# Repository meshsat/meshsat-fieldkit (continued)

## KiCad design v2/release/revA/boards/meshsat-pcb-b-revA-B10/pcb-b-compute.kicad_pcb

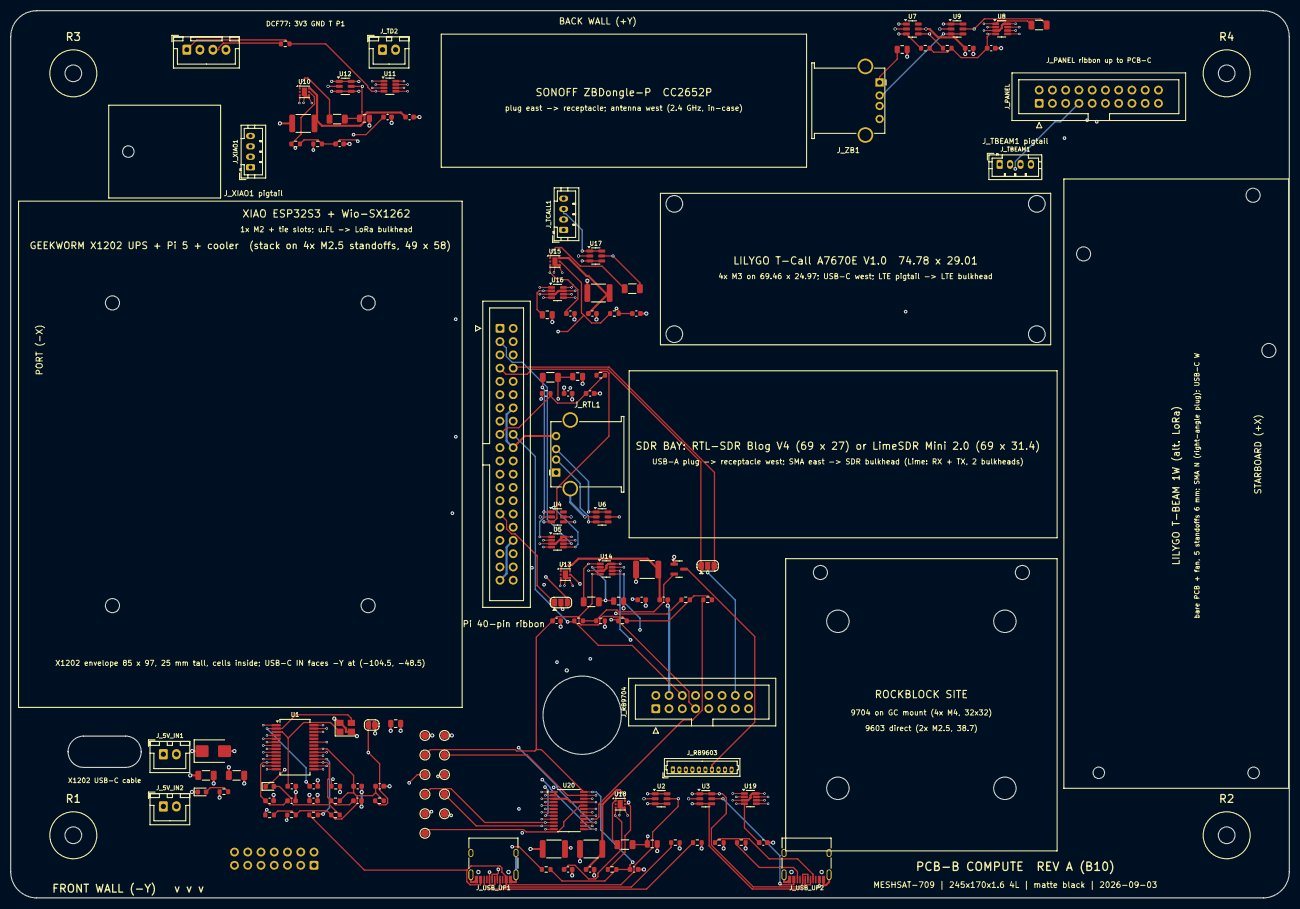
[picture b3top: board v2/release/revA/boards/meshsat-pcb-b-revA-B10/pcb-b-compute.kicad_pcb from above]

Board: 4 copper layers, 245.0 x 170.0 mm, 161 parts (1 on the bottom side), 98 nets.

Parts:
C1, C2: 100u 10V; C_1206_3216Metric
C3, C4: 22p; C_0603_1608Metric
C5, C7, C9, C12, C14, C16, C18, C21, C24, C26, C33, C34: 100n; C_0603_1608Metric
C6, C8, C11, C29, C30, C31, C32: 1u; C_0603_1608Metric
C10, C13, C15, C17, C19, C22, C25: 10u; C_0805_2012Metric
C20, C23, C27, C28: 1n; C_0603_1608Metric
D1: SMBJ5.0A; D_SMB
F2, F4, F5: 2A hold 1812; Fuse_1812_4532Metric
F3: 1.1A hold 1812; Fuse_1812_4532Metric
F6: 0.5A hold 1812; Fuse_1812_4532Metric
H1: M3 rod R1; MountingHole_3.2mm_M3
H2: M3 rod R2; MountingHole_3.2mm_M3
H3: M3 rod R3; MountingHole_3.2mm_M3
H4: M3 rod R4; MountingHole_3.2mm_M3
H5, H6, H7, H8: M2.5 standoff, Pi/X1202 stack; MountingHole_2.7mm_M2.5
H9, H10, H11, H12: M3, T-Call corner; MountingHole_3.2mm_M3
H13, H14, H15: M2.5 standoff, T-Beam 1W; MountingHole_2.7mm_M2.5
H16, H17: M2 standoff, T-Beam 1W; MountingHole_2.2mm_M2
H18: M2 standoff, Wio-SX1262; MountingHole_2.2mm_M2
H19, H20, H21, H22: M4, GC 9704 bracket; MountingHole_4.3mm_M4
H23, H24: M2.5, RockBLOCK 9603; MountingHole_2.7mm_M2.5
JP1: BUSJ to GND = bus-powered; SolderJumper-2_P1.3mm_Open_RoundedPad1.0x1.5mm
JP3: UART TX select: A=UART2 (BCM4) B=UART0 (BCM14); SolderJumper-3_P1.3mm_Open_RoundedPad1.0x1.5mm
JP4: UART RX select: A=UART2 (BCM5) B=UART0 (BCM15); SolderJumper-3_P1.3mm_Open_RoundedPad1.0x1.5mm
J_5V_IN1, J_5V_IN2: X1202 5V OUT (XH2.54); JST_XH_B2B-XH-A_1x02_P2.50mm_Vertical
J_AB1: A-B interconnect (IDC 2x7, underside); IDC-Header_2x07_P2.54mm_Vertical
J_DCF77: DCF77 remote (XH2.5): 3V3 GND T P1; JST_XH_B4B-XH-A_1x04_P2.50mm_Vertical
J_GPIO1: Pi 5 GPIO ribbon 2x20; IDC-Header_2x20_P2.54mm_Vertical
J_PANEL: panel ribbon to PCB-C (IDC 2x10); IDC-Header_2x10_P2.54mm_Vertical
J_RB9603: RockBLOCK 9603 PicoBlade 10; Molex_PicoBlade_53047-1010_1x10_P1.25mm_Vertical
J_RB9704: RockBLOCK 9704 16-pin (IDC 2x8); IDC-Header_2x08_P2.54mm_Vertical
J_RTL1: USB-A receptacle RTL-SDR; USB_A_Stewart_SS-52100-001_Horizontal
J_TBEAM1: USB-C pigtail header (JST-PH 2.0): VBUS D- D+ GND; JST_PH_B4B-PH-K_1x04_P2.00mm_Vertical
J_TCALL1: USB-C pigtail header (JST-PH 2.0): VBUS D- D+ GND; JST_PH_B4B-PH-K_1x04_P2.00mm_Vertical
J_TD2: Touch Display 2 5V (XH2.54); JST_XH_B2B-XH-A_1x02_P2.50mm_Vertical
J_USB_UP1, J_USB_UP2: USB-C 2.0 receptacle; USB_C_Receptacle_HRO_TYPE-C-31-M-12
J_XIAO1: USB-C pigtail header (JST-PH 2.0): VBUS D- D+ GND; JST_PH_B4B-PH-K_1x04_P2.00mm_Vertical
J_ZB1: USB-A receptacle ZigBee; USB_A_Stewart_SS-52100-001_Horizontal
LED1: green 5V; LED_0603_1608Metric
LED2: amber hub; LED_0603_1608Metric
Q1: 2N7002 (SOT-23) OnOff open-drain buffer; SOT-23
R1, R8: 1k; R_0603_1608Metric
R2: 2.7k 1% (REXT, verify datasheet); R_0603_1608Metric
R3, R4, R5, R6, R13, R15, R17, R20, R25, R28, R29: 10k; R_0603_1608Metric
R7: 4.7k; R_0603_1608Metric
R9, R10, R11, R12: 5.1k; R_0603_1608Metric
R14, R16: 0.1R 1% 1206; R_1206_3216Metric
R18, R21, R22, R24: 0.05R 1% 1206; R_1206_3216Metric
R26: 100R; R_0603_1608Metric
R27, R30, R31, R32, R33, R34, R35: 100k; R_0603_1608Metric
S_RTL1, S_RTL2, S_RTL3, S_RTL4: tie slot; Slot_5x1.8_NPTH
S_XIAO1, S_XIAO2: tie slot; Slot_5x1.8_NPTH
S_ZB1, S_ZB2, S_ZB3, S_ZB4: tie slot; Slot_5x1.8_NPTH
TP1: +5V; TestPoint_Pad_D1.5mm
TP2: GND; TestPoint_Pad_D1.5mm
TP3: +3V3; TestPoint_Pad_D1.5mm
TP4: SDA; TestPoint_Pad_D1.5mm
TP5: SCL; TestPoint_Pad_D1.5mm
TP6: EXP_SPARE0; TestPoint_Pad_D1.5mm
TP7: EXP_SPARE1; TestPoint_Pad_D1.5mm
TP8: EXP_SPARE2; TestPoint_Pad_D1.5mm
TP9: EXP_SPARE3; TestPoint_Pad_D1.5mm
TP10: EXP_SPARE4; TestPoint_Pad_D1.5mm
TP11: TX_INHIBIT_n; TestPoint_Pad_D1.5mm
U1: FE1.1s; SSOP-28_5.3x10.2mm_P0.65mm
U2, U3, U6, U9, U12, U17: USBLC6-2SC6; SOT-23-6
U4, U7: TPS2065CDBV; SOT-23-6
U5, U8, U11, U14, U16, U19: INA219AIDCN; SOT-23-8
U10, U13, U15, U18: TPS22810DRV; WSON-6-1EP_2x2mm_P0.65mm_EP1x1.6mm
U20: PCA9555PW; TSSOP-24_4.4x7.8mm_P0.65mm
Y1: 12 MHz 3225; Crystal_SMD_3225-4Pin_3.2x2.5mm

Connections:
+3V3: C12.1, C14.1, C16.1, C18.1, C21.1, C24.1, C26.1, J_DCF77.1, J_GPIO1.1, J_GPIO1.17, J_PANEL.20, R13.2, R15.2, R17.2, R20.2, R25.2, R28.2, R29.2, R30.2, R31.2, R32.2, R33.2, R34.2, R35.2, TP3.1, U5.4, U8.4, U8.7, U11.4, U11.7, U11.8, U14.4, U16.4, U16.8, U19.4, U20.24
+5V: C1.1, C2.1, C9.1, C10.1, C33.1, C34.1, D1.1, F2.1, F3.1, F4.1, F5.1, F6.1, J_5V_IN1.1, J_5V_IN2.1, J_TD2.1, R1.1, TP1.1, U1.20, U4.5, U7.5
/5V_A: C25.1, J_AB1.1, J_AB1.2, R24.2, U19.2
/5V_RB: C19.1, J_RB9603.8, J_RB9704.15, R21.2, U14.2
/5V_RTL: C13.1, J_RTL1.1, R14.2, U5.2, U6.5
/5V_TC: C22.1, J_TCALL1.1, R22.2, U16.2, U17.5
/5V_XIAO: C17.1, J_TBEAM1.1, J_XIAO1.1, R18.2, U11.2, U12.5
/5V_ZB: C15.1, J_ZB1.1, R16.2, U8.2, U9.5
/A_CT: C23.1, U18.3
/A_FUSED: C32.1, F3.2, U18.6
/BANK_ALERT: J_AB1.12, J_GPIO1.11, U20.17
/CC1_UP: J_USB_UP1.A5, R9.1
/CC1_UP2: J_USB_UP2.A5, R11.1
/CC2_UP: J_USB_UP1.B5, R10.1
/CC2_UP2: J_USB_UP2.B5, R12.1
/DCF_PON: J_DCF77.4, J_GPIO1.35
/DCF_T: J_DCF77.3, J_GPIO1.40, R29.1
/EN_A: R35.1, U18.5, U20.9
/EN_RB: R33.1, U13.5, U20.7
/EN_RTL: R30.1, U4.4, U20.4
/EN_TC: R34.1, U15.5, U20.8
/EN_XIAO: R32.1, U10.5, U20.6
/EN_ZB: R31.1, U7.4, U20.5
/EPD_DC: J_GPIO1.21, J_PANEL.8
/EPD_RES_ALT: J_GPIO1.26, J_PANEL.15
/EXP_INT: J_AB1.9, J_GPIO1.22, J_PANEL.6, R25.1, U20.1
/EXP_SPARE0: TP6.1, U20.10
/EXP_SPARE1: TP7.1, U20.11
/EXP_SPARE2: TP8.1, U20.18
/EXP_SPARE3: TP9.1, U20.19
/EXP_SPARE4: TP10.1, U20.20
/FLT_RB: R20.1, U20.16
/FLT_RTL: R13.1, U4.3, U20.13
/FLT_XIAO: R17.1, U20.15
/FLT_ZB: R15.1, U7.3, U20.14
/HUB_BUSJ: JP1.1, R4.1, U1.19
/HUB_LED1: LED2.1, U1.23
/HUB_OVCJ: R6.1, U1.26
/HUB_REXT: R2.1, U1.14
/HUB_RST: C11.1, R3.1, U1.17
/HUB_TESTJ: R5.1, U1.27
/HUB_VBUSM: R7.2, U1.18
/HUB_VD18: C7.1, C8.1, U1.12, U1.28
/HUB_VD33: C5.1, C6.1, R3.2, R4.2, R5.2, R6.2, R8.1, U1.13, U1.21
/LED_5V_A: LED1.2, R1.2
/LED_HUB_A: LED2.2, R8.2
/PANEL_5V: F6.2, J_PANEL.1, J_PANEL.2
/PANEL_PWM: J_GPIO1.32, J_PANEL.17
/PWM1: J_GPIO1.33, J_PANEL.16
/Q1_G: Q1.2, R26.2, R27.1
/RB_CT: C28.1, U13.3
/RB_CTRL: J_GPIO1.18, J_RB9704.6, R26.1
/RB_FUSED: C30.1, F5.2, U13.6
/RB_IEN: J_GPIO1.37, J_RB9704.3
/RB_NETAV: J_GPIO1.15, J_RB9603.4
/RB_ONOFF: J_RB9603.7, Q1.3
/RB_STATUS: J_GPIO1.16, J_RB9603.5, J_RB9704.7, R28.1
/RB_XMTG: J_GPIO1.12, J_RB9704.8
/SCL: J_AB1.8, J_GPIO1.5, J_PANEL.5, TP5.1, U5.5, U8.5, U11.5, U14.5, U16.5, U19.5, U19.7, U20.22
/SDA: J_AB1.7, J_GPIO1.3, J_PANEL.4, TP4.1, U5.6, U8.6, U11.6, U14.6, U14.7, U16.6, U19.6, U20.23
/SPI_CE0: J_GPIO1.24, J_PANEL.14
/SPI_MOSI: J_GPIO1.19, J_PANEL.12
/SPI_SCLK: J_GPIO1.23, J_PANEL.10
/SW_A: R24.1, U18.1, U19.1
/SW_RB: R21.1, U13.1, U14.1
/SW_RTL: R14.1, U4.1, U5.1
/SW_TC: R22.1, U15.1, U16.1
/SW_XIAO: R18.1, U10.1, U11.1
/SW_ZB: R16.1, U7.1, U8.1
/TC_CT: C20.1, U15.3
/TC_FUSED: C31.1, F2.2, U15.6
/TR_APRS: J_AB1.10, J_GPIO1.13, J_PANEL.7
/TX_INHIBIT_n: J_AB1.14, J_PANEL.19, TP11.1
/UART0_RX: JP4.3, J_GPIO1.10
/UART0_TX: JP3.3, J_GPIO1.8
/UART2_RX: JP4.1, J_GPIO1.29
/UART2_TX: JP3.1, J_GPIO1.7
/UART_RX_M: JP4.2, J_RB9603.1, J_RB9704.13
/UART_TX_M: JP3.2, J_RB9603.6, J_RB9704.14
/USB_A_N: J_AB1.5, J_USB_UP2.A7, J_USB_UP2.B7, U3.3, U3.4
/USB_A_P: J_AB1.4, J_USB_UP2.A6, J_USB_UP2.B6, U3.1, U3.6
/USB_RTL_N: J_RTL1.2, U1.10, U6.3, U6.4
/USB_RTL_P: J_RTL1.3, U1.11, U6.1, U6.6
/USB_TC_N: J_TCALL1.2, U1.6, U17.3, U17.4
/USB_TC_P: J_TCALL1.3, U1.7, U17.1, U17.6
/USB_UP_N: J_USB_UP1.A7, J_USB_UP1.B7, U1.15, U2.3, U2.4
/USB_UP_P: J_USB_UP1.A6, J_USB_UP1.B6, U1.16, U2.1, U2.6
/USB_UP_VBUS: J_USB_UP1.A4, J_USB_UP1.A9, J_USB_UP1.B4, J_USB_UP1.B9, R7.1, U2.5
/USB_XIAO_N: J_TBEAM1.2, J_XIAO1.2, U1.4, U12.3, U12.4
/USB_XIAO_P: J_TBEAM1.3, J_XIAO1.3, U1.5, U12.1, U12.6
/USB_ZB_N: J_ZB1.2, U1.8, U9.3, U9.4
/USB_ZB_P: J_ZB1.3, U1.9, U9.1, U9.6
/VBUS_A_SENSE: J_AB1.11, J_USB_UP2.A4, J_USB_UP2.A9, J_USB_UP2.B4, J_USB_UP2.B9, U3.5
/XIAO_CT: C27.1, U10.3
/XIAO_FUSED: C29.1, F4.2, U10.6
/XIN: C3.1, U1.3, Y1.1
/XOUT: C4.1, U1.2, Y1.3
GND: C1.2, C2.2, C3.2, C4.2, C5.2, C6.2, C7.2, C8.2, C9.2, C10.2, C11.2, C12.2, C13.2, C14.2, C15.2, C16.2, C17.2, C18.2, C19.2, C20.2, C21.2, C22.2, C23.2, C24.2, C25.2, C26.2, C27.2, C28.2, C29.2, C30.2, C31.2, C32.2, C33.2, C34.2, D1.2, JP1.2, J_5V_IN1.2, J_5V_IN2.2, J_AB1.3, J_AB1.6, J_AB1.13, J_DCF77.2, J_GPIO1.6, J_GPIO1.9, J_GPIO1.14, J_GPIO1.20, J_GPIO1.25, J_GPIO1.30, J_GPIO1.34, J_GPIO1.39, J_PANEL.3, J_PANEL.9, J_PANEL.11, J_PANEL.13, J_PANEL.18, J_RB9603.10, J_RB9704.1, J_RB9704.4, J_RB9704.10, J_RB9704.16, J_RTL1.4, J_RTL1.5, J_TBEAM1.4, J_TCALL1.4, J_TD2.2, J_USB_UP1.A1, J_USB_UP1.A12, J_USB_UP1.B1, J_USB_UP1.B12, J_USB_UP1.S1, J_USB_UP2.A1, J_USB_UP2.A12, J_USB_UP2.B1, J_USB_UP2.B12, J_USB_UP2.S1, J_XIAO1.4, J_ZB1.4, J_ZB1.5, LED1.1, Q1.1, R2.2, R9.2, R10.2, R11.2, R12.2, R27.2, TP2.1, U1.1, U2.2, U3.2, U4.2, U5.3, U5.7, U5.8, U6.2, U7.2, U8.3, U8.8, U9.2, U10.4, U10.7, U11.3, U12.2, U13.4, U13.7, U14.3, U14.8, U15.4, U15.7, U16.3, U16.7, U17.2, U18.4, U18.7, U19.3, U19.8, U20.2, U20.3, U20.12, U20.21, Y1.2, Y1.4

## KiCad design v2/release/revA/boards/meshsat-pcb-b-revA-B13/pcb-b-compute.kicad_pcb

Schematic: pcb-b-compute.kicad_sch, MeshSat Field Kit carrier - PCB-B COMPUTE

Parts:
BT1: CR2032 holder Keystone 3034 (VBAT, also the NEO-M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; BatteryHolder_Keystone_3034_1x20mm
C1, C2, C40, C41, C42, C43, C44: 100u 10V; C_1206_3216Metric
C3, C4: 27p; C_0603_1608Metric
C5, C6, C7, C8, C9, C10, C11, C15, C16, C18, C26, C27, C31, C35, C39, C51, C54, C55, C59, C60, C63, C65: 100n; C_0603_1608Metric
C12, C13, C14, C30: 1u; C_0603_1608Metric
C17, C19, C32, C36, C45, C46, C47, C48, C49, C61, C64, C66: 10u; C_0805_2012Metric
C28: 1n; C_0603_1608Metric
C33, C34, C37, C38: 22u 10V X7R 1210; C_1210_3225Metric
C50: 100u 6.3V; C_1206_3216Metric
C52, C56, C57, C58: 33p; C_0402_1005Metric
C53: 10p; C_0402_1005Metric
C62: 47p; C_0402_1005Metric
D1, D3, D4: SMBJ5.0A; D_SMB
F5: 2A hold 1812; Fuse_1812_4532Metric
F6, F7: 0.5A hold 1812; Fuse_1812_4532Metric
J_5V_M1: 5 V rail M1 from PCB-A J_5V_M1 (JST-VH, 18 AWG): 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; JST_VH_B2P-VH_1x02_P3.96mm_Vertical
J_5V_M2: 5 V rail M2 from PCB-A J_5V_M2 (JST-VH, 18 AWG): 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; JST_VH_B2P-VH_1x02_P3.96mm_Vertical
J_5V_PI: Pi rail 5.1 V 5 A from PCB-A J_5V_PI (JST-VH, 18 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; JST_VH_B2P-VH_1x02_P3.96mm_Vertical
J_AB1: A-B interconnect (IDC 2x9, underside); IDC-Header_2x09_P2.54mm_Vertical
J_DBG: console UART0 (GPIO14/15, 3.3 V): GND TX RX; PinHeader_1x03_P2.54mm_Vertical
J_DCF77: DCF77 remote (XH2.5): 3V3 GND T P1; JST_XH_B4B-XH-A_1x04_P2.50mm_Vertical
J_DISP: Touch Display 2 FPC 22-pin 0.5 mm (Hirose FH12-22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; Hirose_FH12-22S-0.5SH_1x22-1MP_P0.50mm_Horizontal
J_FAN: CM5 cooler fan (JST-SH 1.0): 5V GND TACHO PWM; 5 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; JST_SH_BM04B-SRSS-TB_1x04-1MP_P1.00mm_Vertical
J_FLASH: USB-C 2.0 receptacle; USB_C_Receptacle_HRO_TYPE-C-31-M-12; LCSC C165948
J_GNSS1: U.FL to the GNSS bulkhead pigtail; U.FL_Hirose_U.FL-R-SMT-1_Vertical
J_LTE1: mini PCIe socket 52P H4.0 + 2x M2.5 standoffs: Qu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; MiniPCIe_Socket_52P_H4.0_Standoff
J_LTEDBG: EG25-G main UART (3.3 V, bench): GND TX RX; PinHeader_1x03_P2.54mm_Vertical
J_PANEL: panel ribbon to PCB-C (IDC 2x10); IDC-Header_2x10_P2.54mm_Vertical
J_PMIC: PMIC_Enable: short to force the module off (bench); PinHeader_1x02_P2.54mm_Vertical
J_PWRBTN: PWR_Button: momentary to GND wakes the module fro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; PinHeader_1x02_P2.54mm_Vertical
J_RB9603: RockBLOCK 9603 PicoBlade 10; Molex_PicoBlade_53047-1010_1x10_P1.25mm_Vertical
J_RB9704: RockBLOCK 9704 16-pin (IDC 2x8); IDC-Header_2x08_P2.54mm_Vertical
J_RPIBOOT: nRPIBOOT jumper: fit to flash the eMMC over J_FLA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; PinHeader_1x02_P2.54mm_Vertical
J_RTL1: USB-A receptacle RTL-SDR; USB_A_Stewart_SS-52100-001_Horizontal
J_SIM1: nano-SIM push-push GCT SIM8060; nanoSIM_GCT_SIM8060-6-0-14-00
J_TD2: Touch Display 2 5V (XH2.54); JST_XH_B2B-XH-A_1x02_P2.50mm_Vertical
J_WP: EEPROM_nWP jumper: fit to write-protect the bootl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; PinHeader_1x02_P2.54mm_Vertical
J_ZBDBG: CC2652P cJTAG (bench): 3V3 GND TMSC TCKC RESET; PinHeader_1x05_P2.54mm_Vertical
L31, L32: 3.3uH XAL4020-332MEB; L_Coilcraft_XAL4020-XXX
L40: 27nH 0402 (antenna bias tee); L_0402_1005Metric
LED1: green 5V; LED_0603_1608Metric
LED2: amber LTE network (LED_WWAN# sinks); LED_0603_1608Metric
LED3: red ZigBee (DIO_7); LED_0603_1608Metric
LED4: green ZigBee (DIO_8); LED_0603_1608Metric
LED5: green ACT (LED_nACT sinks); LED_0603_1608Metric
LED6: red PWR; LED_0603_1608Metric
Q1: 2N7002 OnOff open-drain buffer; SOT-23; LCSC C8545
Q2: BC857: LED_nPWR must be buffered (datasheet Table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; SOT-23
Q3, Q4, Q5: 2N7002; SOT-23; LCSC C8545
R1, R46, R48, R64, R70, R71: 1k; R_0603_1608Metric
R2: 12.0k 1% (RBIAS); R_0603_1608Metric
R3, R4, R5, R6, R7, R8, R13, R25, R28, R29, R47, R49, R52, R53, R54, R56, R61, R62, R63, R65, R67, R68, R69: 10k; R_0603_1608Metric
R14: 0.1R 1% 1206; R_1206_3216Metric
R21, R41: 0.05R 1% 1206; R_1206_3216Metric
R26: 100R; R_0603_1608Metric
R27, R30, R33, R37, R38, R42: 100k; R_0603_1608Metric
R35, R39: 33.2k 1%; R_0603_1608Metric
R36, R40: 10k 1%; R_0603_1608Metric
R50, R51: 5.1k; R_0603_1608Metric
R55, R59, R60: 4.7k; R_0603_1608Metric
R57, R58: 2.2k; R_0603_1608Metric
R66: 10R; R_0603_1608Metric
TP1: +5V_M1; TestPoint_Pad_D1.5mm
TP2: GND; TestPoint_Pad_D1.5mm
TP3: +3V3; TestPoint_Pad_D1.5mm
TP4: SDA; TestPoint_Pad_D1.5mm
TP5: SCL; TestPoint_Pad_D1.5mm
TP6: TX_INHIBIT_n; TestPoint_Pad_D1.5mm
TP7: PI_KILL; TestPoint_Pad_D1.5mm
TP8: +5V_M2; TestPoint_Pad_D1.5mm
TP9: +5V_PI; TestPoint_Pad_D1.5mm
TP10: +3V3_CM; TestPoint_Pad_D1.5mm
TP11: +1V8_CM; TestPoint_Pad_D1.5mm
TP12: VBUS_EN; TestPoint_Pad_D1.5mm
TP13: PMIC_EN; TestPoint_Pad_D1.5mm
TP14: PWR_BUT; TestPoint_Pad_D1.5mm
TP15: GNSS_PPS; TestPoint_Pad_D1.5mm
TP16: GNSS_TXD; TestPoint_Pad_D1.5mm
TP17: I2S_BCLK; TestPoint_Pad_D1.5mm
TP18: I2S_LRCLK; TestPoint_Pad_D1.5mm
TP19: VBUS_FLASH; TestPoint_Pad_D1.5mm
TP20: SDA_CM; TestPoint_Pad_D1.5mm
TP21: SCL_CM; TestPoint_Pad_D1.5mm
TP22: +3V3_LTE; TestPoint_Pad_D1.5mm
TP23: EXP_INT; TestPoint_Pad_D1.5mm
TP30: EXP_SPARE0; TestPoint_Pad_D1.5mm
TP31: EXP_SPARE1; TestPoint_Pad_D1.5mm
TP32: EXP_SPARE2; TestPoint_Pad_D1.5mm
TP33: EXP_SPARE3; TestPoint_Pad_D1.5mm
TP34: EXP_SPARE4; TestPoint_Pad_D1.5mm
TP35: EXP_SPARE5; TestPoint_Pad_D1.5mm
TP36: EXP_SPARE6; TestPoint_Pad_D1.5mm
TP37: EXP_SPARE7; TestPoint_Pad_D1.5mm
TP38: EXP_SPARE8; TestPoint_Pad_D1.5mm
TP39: EXP_SPARE9; TestPoint_Pad_D1.5mm
TP40: EXP_SPARE10; TestPoint_Pad_D1.5mm
U1: USB2517I-JZX seven-port USB 2.0 hub (strap defaul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; QFN-64-1EP_9x9mm_P0.5mm_EP4.7x4.7mm; LCSC C1521556
U2, U6, U7, U8, U9, U10: USBLC6-2SC6; SOT-23-6; LCSC C7519
U4: TPS2065CDBV; SOT-23-5
U5, U14, U33: INA219AIDCN; SOT-23-8; LCSC C138024
U13: TPS22810DRV; WSON-6-1EP_2x2mm_P0.65mm_EP1x1.6mm
U20: PCA9555PW 0x20; TSSOP-24_4.4x7.8mm_P0.65mm; LCSC C5626
U21: PCA9555PW 0x25; TSSOP-24_4.4x7.8mm_P0.65mm; LCSC C5626
U30A: Amphenol 10164227-1004A1RLF receptacle A (CM5 pin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; CM5_Conn_A_10164227; LCSC C7435219
U30B: Amphenol 10164227-1004A1RLF receptacle B (CM5 pin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; CM5_Conn_B_10164227; LCSC C7435219
U31: TPS563201 3.3 V buck from M1 for the board (follo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; SOT-23-6
U32: TPS563201 3.3 V buck for the LTE socket (EN_LTE); SOT-23-6
U34: TCA9517A I2C buffer: A = module (GPIO2/3, +3V3_CM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; MSOP-8_3x3mm_P0.65mm
U40: u-blox NEO-M9N-00B: I2C + PPS, external active an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; ublox_NEO
U41: Seeed Wio-SX1262: 1 RF_SW 2 MISO 3 MOSI 4 SCK 5 N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; Seeed_Wio-SX1262
U42: Ebyte E72-2G4M20S1E CC2652P ZigBee coordinator (Z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; Ebyte_E72-2G4M20S1E
Y1: 24 MHz 3225; Crystal_SMD_3225-4Pin_3.2x2.5mm

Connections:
+3V3: C5.1, C6.1, C7.1, C8.1, C9.1, C10.1, C11.1, C14.1, C16.1, C18.1, C26.1, C27.1, C33.1, C34.1, C55.1, C60.1, C61.1, C63.1, C64.1, C65.1, C66.1, F7.1, J_DCF77.1, J_PANEL.20, J_ZBDBG.1, L31.2, R5.2, R6.2, R7.2, R8.2, R13.2, R25.2, R28.2, R29.2, R30.2, R33.2, R35.1, R57.2, R58.2, R62.2, R63.2, R65.2, R67.2, R68.2, R69.2, TP3.1, U1.5, U1.10, U1.21, U1.22, U1.24, U1.27, U1.35, U1.43, U1.44, U1.46, U1.52, U1.57, U1.64, U2.5 (VBUS), U5.4 (VS), U7.5 (VBUS), U14.4 (VS), U20.24 (VDD), U21.3 (A2), U21.21 (A0), U21.24 (VDD), U33.4 (VS), U33.8 (A1), U34.8 (VCCB), U40.23 (VCC), U41.8, U42.20
/5V_LTE_IN: C36.1, R41.2, U32.3 (VIN), U33.2 (IN-)
/5V_RB: C19.1, J_RB9603.8, J_RB9704.15, R21.2, U14.2 (IN-)
/5V_RTL: C17.1, J_RTL1.1 (VBUS), R14.2, U5.2 (IN-), U6.5 (VBUS)
/+1V8_CM: TP11.1, U30A.88 (CM5_1.8V), U30A.90 (CM5_1.8V)
/+3V3_AB: F7.2, J_AB1.17
/+3V3_CM: C39.1, C49.1, C54.1, J_DISP.22, Q2.2 (E), Q3.1 (G), Q4.1 (G), Q5.1 (G), R37.1, R46.1, R49.2, R52.2, R53.2, R54.2, R56.2, TP10.1, U10.5 (VBUS), U30A.78 (GPIO_VREF), U30A.84 (CM5_3.3V), U30A.86 (CM5_3.3V), U34.4 (GND)
/+3V3_LTE: C37.1, C38.1, C50.1, C51.1, C52.1, C53.1, J_LTE1.2, J_LTE1.39, J_LTE1.41, J_LTE1.52, L32.2, R39.1, R59.2, R60.2, R64.1, TP22.1, U8.5 (VBUS)
/+5V_M1: C1.1, C2.1, C32.1, D1.1 (A1), F6.1, J_5V_M1.1, J_TD2.1, R1.1, R41.1, TP1.1, U31.3 (VIN), U33.1 (IN+)
/+5V_M2: C15.1, C40.1, C41.1, D3.1 (A1), F5.1, J_5V_M2.1, TP8.1, U4.5 (IN)
/+5V_PI: C42.1, C43.1, C44.1, C45.1, C46.1, C47.1, C48.1, D4.1 (A1), J_5V_PI.1, J_FAN.1, TP9.1, U30A.77 (5V), U30A.79 (5V), U30A.81 (5V), U30A.83 (5V), U30A.85 (5V), U30A.87 (5V)
/BST33: C31.1, U31.6 (VBST)
/BST_LTE: C35.1, U32.6 (VBST)
/BT_nDIS: U21.5 (IO0_1), U30A.91 (BT_nDisable)
/CAM_GPIO0: J_DISP.17, U30A.97 (CAM_GPIO0)
/CC1_F: J_FLASH.A5 (CC1), R50.1
/CC2_F: J_FLASH.B5 (CC2), R51.1
/DCF_PON: J_DCF77.4, U21.6 (IO0_2)
/DCF_T: J_DCF77.3, R29.1, U21.13 (IO1_0)
/DISP_SCL: J_DISP.20, U10.3 (I/O2), U10.4 (I/O2), U30A.80 (SCL0)
/DISP_SDA: J_DISP.21, U10.1 (I/O1), U10.6 (I/O1), U30A.82 (SDA0)
/DSI0_C_N: J_DISP.8, U30B.127 (MIPI0_C_N)
/DSI0_C_P: J_DISP.9, U30B.129 (MIPI0_C_P)
/DSI0_D0_N: J_DISP.2, U30B.115 (MIPI0_D0_N)
/DSI0_D0_P: J_DISP.3, U30B.117 (MIPI0_D0_P)
/DSI0_D1_N: J_DISP.5, U30B.121 (MIPI0_D1_N)
/DSI0_D1_P: J_DISP.6, U30B.123 (MIPI0_D1_P)
/DSI0_D2_N: J_DISP.11, U30B.133 (MIPI0_D2_N)
/DSI0_D2_P: J_DISP.12, U30B.135 (MIPI0_D2_P)
/DSI0_D3_N: J_DISP.14, U30B.139 (MIPI0_D3_N)
/DSI0_D3_P: J_DISP.15, U30B.141 (MIPI0_D3_P)
/EEPROM_nWP: J_WP.1, U30A.20 (EEPROM_nWP)
/EN33: R37.2, R38.1, U31.5 (EN)
/EN_I2C: R56.1, U34.5 (EN)
/EN_LTE: R42.1, U20.5 (IO0_1), U32.5 (EN)
/EN_RB: R33.1, U13.5 (EN/UVLO)
/EN_RTL: R30.1, U4.4 (EN), U20.4 (IO0_0)
/EPD_DC: J_PANEL.8, U30A.29 (GPIO16)
/EPD_RES_ALT: J_PANEL.15, U21.7 (IO0_3)
/EXP_INT: J_AB1.9, J_PANEL.6, R25.1, TP23.1, U20.1 (~INT), U21.1 (~INT), U30A.41 (GPIO25)
/EXP_SPARE0: TP30.1, U21.8 (IO0_4)
/EXP_SPARE1: TP31.1, U21.9 (IO0_5)
/EXP_SPARE2: TP32.1, U21.10 (IO0_6)
/EXP_SPARE3: TP33.1, U21.11 (IO0_7)
/EXP_SPARE4: TP34.1, U21.14 (IO1_1)
/EXP_SPARE5: TP35.1, U21.15 (IO1_2)
/EXP_SPARE6: TP36.1, U21.16 (IO1_3)
/EXP_SPARE7: TP37.1, U21.17 (IO1_4)
/EXP_SPARE8: TP38.1, U21.18 (IO1_5)
/EXP_SPARE9: TP39.1, U21.19 (IO1_6)
/EXP_SPARE10: TP40.1, U21.20 (IO1_7)
/FAN_PWM: J_FAN.4, R49.1, U30A.19 (Fan_PWM)
/FAN_TACHO: J_FAN.3, U30A.16 (Fan_Tacho)
/FB33: R35.2, R36.1, U31.4 (VFB)
/FB_LTE: R39.2, R40.1, U32.4 (VFB)
/FLT_RTL: R13.1, U1.28, U4.3 (~FLT), U20.13 (IO1_0)
/GNSS_ANT: C62.1, J_GNSS1.1 (In), L40.2
/GNSS_BIAS: L40.1, R66.2
/GNSS_PPS: TP15.1, U30A.46 (GPIO22), U40.3 (TIMEPULSE)
/GNSS_RF_IN: C62.2, U40.11 (RF_IN)
/GNSS_TXD: TP16.1, U40.20 (TXD/SPI_MISO)
/GNSS_VCC_RF: R66.1, U40.9 (VCC_RF)
/GNSS_nRST: R65.1, U20.11 (IO0_7), U40.8 (~RESET)
/HUB_CFG0: R3.1, U1.41
/HUB_CFG1: R4.1, U1.42
/HUB_DIS6M: R5.1, U1.53
/HUB_DIS6P: R6.1, U1.54
/HUB_DIS7M: R7.1, U1.55
/HUB_DIS7P: R8.1, U1.56
/HUB_RBIAS: R2.1, U1.63
/HUB_VD18: C12.1, U1.25
/HUB_VD18PLL: C13.1, U1.62
/I2S_BCLK: J_AB1.11, TP17.1, U30A.49 (GPIO18)
/I2S_DIN: J_AB1.16, U30A.27 (GPIO20)
/I2S_DOUT: J_AB1.15, U30A.25 (GPIO21)
/I2S_LRCLK: J_AB1.12, TP18.1, U30A.26 (GPIO19)
/LED_5V_A: LED1.2 (A), R1.2
/LED_ACT_A: LED5.2 (A), R46.2
/LED_LTE_A: LED2.2 (A), R64.2
/LED_PWR_A: LED6.2 (A), R48.2
/LED_ZBG_A: LED4.2 (A), R71.2
/LED_ZBR_A: LED3.2 (A), R70.2
/LED_nACT: LED5.1 (K), U30A.21 (LED_nACT)
/LED_nPWR: R47.1, U30A.95 (LED_nPWR)
/LORA_BUSY: U30A.47 (GPIO23), U41.11
/LORA_DIO1: U30A.45 (GPIO24), U41.12
/LORA_NRST: U30A.24 (GPIO26), U41.5
/LORA_NSS: R67.1, U30A.37 (GPIO7), U41.6
/LTE_DTR: J_LTE1.31, R61.1, U20.8 (IO0_4)
/LTE_PERST_n: J_LTE1.22, R60.1, U20.7 (IO0_3)
/LTE_RI: J_LTE1.17, R62.1, U20.14 (IO1_1)
/LTE_UART_RX: J_LTE1.11, J_LTEDBG.3
/LTE_UART_TX: J_LTE1.13, J_LTEDBG.2
/LTE_WAKE_n: J_LTE1.1, R63.1, U20.15 (IO1_2)
/LTE_W_DIS_n: J_LTE1.20, R59.1, U20.6 (IO0_2)
/LTE_nLED: J_LTE1.42, LED2.1 (K)
/PANEL_5V: F6.2, J_PANEL.1, J_PANEL.2
/PANEL_PWM: J_PANEL.17, U30A.31 (GPIO12)
/PI_KILL: J_AB1.2, Q4.3 (D), TP7.1
/PI_KILL_CM: Q4.2 (S), R53.1, U30A.50 (GPIO17)
/PI_SHDN_REQ: J_AB1.1, Q3.3 (D)
/PI_SHDN_REQ_CM: Q3.2 (S), R52.1, U30A.30 (GPIO6)
/PMIC_EN: J_PMIC.1, TP13.1, U30A.99 (PMIC_Enable)
/PWM1: J_PANEL.16, U30A.28 (GPIO13)
/PWR_BUT: J_PWRBTN.1, TP14.1, U30A.92 (PWR_Button)
/Q1_G: Q1.1 (G), R26.2, R27.1
/Q2_B: Q2.1 (B), R47.2
/Q2_C: Q2.3 (C), R48.1
/RB_CT: C28.1, U13.3 (CT)
/RB_CTRL: J_RB9704.6, R26.1, U20.19 (IO1_6)
/RB_FUSED: C30.1, F5.2, U13.6 (VIN)
/RB_IEN: J_RB9704.3, U20.20 (IO1_7)
/RB_NETAV: J_RB9603.4, U20.17 (IO1_4)
/RB_ONOFF: J_RB9603.7, Q1.3 (D)
/RB_STATUS: J_RB9603.5, J_RB9704.7, R28.1, U20.16 (IO1_3)
/RB_XMTG: J_RB9704.8, U20.18 (IO1_5)
/SCL: J_AB1.8, J_PANEL.5, R58.1, TP5.1, U5.5 (SCL), U14.5 (SCL), U14.7 (A0), U20.22 (SCL), U21.22 (SCL), U33.5 (SCL), U34.6 (SDAB)
/SCL_CM: TP21.1, U30A.56 (GPIO3), U34.3 (SDAA), U40.19 (SCL/SPI_CLK)
/SDA: J_AB1.7, J_PANEL.4, R57.1, TP4.1, U5.6 (SDA), U14.6 (SDA), U20.23 (SDA), U21.23 (SDA), U33.6 (SDA), U34.7 (SCLB)
/SDA_CM: TP20.1, U30A.58 (GPIO2), U34.2 (SCLA), U40.18 (SDA/~SPI_CS)
/SIM_CLK: C57.1, J_LTE1.12, J_SIM1.3 (CLK)
/SIM_IO: C56.1, J_LTE1.10, J_SIM1.7 (I/O)
/SIM_RST: C58.1, J_LTE1.14, J_SIM1.2 (RST)
/SIM_VCC: C59.1, J_LTE1.8, J_SIM1.1 (VCC)
/SPI_CE0: J_PANEL.14, U30A.39 (GPIO8)
/SPI_MISO: U30A.40 (GPIO9), U41.2
/SPI_MOSI: J_PANEL.12, U30A.44 (GPIO10), U41.3
/SPI_SCLK: J_PANEL.10, U30A.38 (GPIO11), U41.4
/SW33: C31.2, L31.1, U31.2 (SW)
/SW_LTE: C35.2, L32.1, U32.2 (SW)
/SW_RB: R21.1, U13.1 (VOUT), U14.1 (IN+)
/SW_RTL: R14.1, U4.1 (OUT), U5.1 (IN+)
/TR_APRS: J_AB1.10, J_PANEL.7, Q5.3 (D), R55.1
/TR_APRS_CM: Q5.2 (S), R54.1, U30A.48 (GPIO27)
/TX_INHIBIT_n: J_AB1.14, J_PANEL.19, TP6.1
/UART0_RX: J_DBG.3, U30A.51 (GPIO15)
/UART0_TX: J_DBG.2, U30A.55 (GPIO14)
/UART1_RX: U30A.35 (ID_SC), U42.8
/UART1_TX: U30A.36 (ID_SD), U42.7
/UART2_RX: J_RB9603.1, J_RB9704.13, U30A.34 (GPIO5)
/UART2_TX: J_RB9603.6, J_RB9704.14, U30A.54 (GPIO4)
/USB_LTE_N: J_LTE1.36, U8.3 (I/O2), U8.4 (I/O2), U30B.165 (USB3-1-DM)
/USB_LTE_P: J_LTE1.38, U8.1 (I/O1), U8.6 (I/O1), U30B.163 (USB3-1-DP)
/USB_OTG_N: J_FLASH.A7 (D-), J_FLASH.B7 (D-), U9.3 (I/O2), U9.4 (I/O2), U30B.103 (USB_N)
/USB_OTG_P: J_FLASH.A6 (D+), J_FLASH.B6 (D+), U9.1 (I/O1), U9.6 (I/O1), U30B.105 (USB_P)
/USB_RTL_N: J_RTL1.2 (D-), U1.1, U6.3 (I/O2), U6.4 (I/O2)
/USB_RTL_P: J_RTL1.3 (D+), U1.2, U6.1 (I/O1), U6.6 (I/O1)
/USB_UP_N: U1.58, U2.3 (I/O2), U2.4 (I/O2), U30B.136 (USB3-0-DM)
/USB_UP_P: U1.59, U2.1 (I/O1), U2.6 (I/O1), U30B.134 (USB3-0-DP)
/USB_WALL_N: J_AB1.5, U1.3, U7.3 (I/O2), U7.4 (I/O2)
/USB_WALL_P: J_AB1.4, U1.4, U7.1 (I/O1), U7.6 (I/O1)
/VBAT: BT1.1 (+), U30A.76 (VBAT), U40.22 (V_BCKP)
/VBUS_EN: TP12.1, U30B.111 (VBUS_EN)
/VBUS_FLASH: J_FLASH.A4 (VBUS), J_FLASH.A9 (VBUS), J_FLASH.B4 (VBUS), J_FLASH.B9 (VBUS), TP19.1, U9.5 (VBUS)
/WL_nDIS: U21.4 (IO0_0), U30A.89 (WL_nDisable)
/XIN: C3.1, U1.61, Y1.1
/XOUT: C4.1, U1.60, Y1.3
/ZB_BSL: R69.1, U20.10 (IO0_6), U42.10
/ZB_LED_G: R71.1, U42.3
/ZB_LED_R: R70.1, U42.2
/ZB_TCKC: J_ZBDBG.4, U42.14
/ZB_TMSC: J_ZBDBG.3, U42.13
/ZB_nRST: J_ZBDBG.5, R68.1, U20.9 (IO0_5), U42.24
/nRPIBOOT: J_RPIBOOT.1, U30A.93 (nRPIBOOT)
GND: BT1.2 (-), C1.2, C2.2, C3.2, C4.2, C5.2, C6.2, C7.2, C8.2, C9.2, C10.2, C11.2, C12.2, C13.2, C14.2, C15.2, C16.2, C17.2, C18.2, C19.2, C26.2, C27.2, C28.2, C30.2, C32.2, C33.2, C34.2, C36.2, C37.2, C38.2, C39.2, C40.2, C41.2, C42.2, C43.2, C44.2, C45.2, C46.2, C47.2, C48.2, C49.2, C50.2, C51.2, C52.2, C53.2, C54.2, C55.2, C56.2, C57.2, C58.2, C59.2, C60.2, C61.2, C63.2, C64.2, C65.2, C66.2, D1.2 (A2), D3.2 (A2), D4.2 (A2), J_5V_M1.2, J_5V_M2.2, J_5V_PI.2, J_AB1.3, J_AB1.6, J_AB1.13, J_AB1.18, J_DBG.1, J_DCF77.2, J_DISP.1, J_DISP.4, J_DISP.7, J_DISP.10, J_DISP.13, J_DISP.16, J_FAN.2, J_FLASH.A1 (GND), J_FLASH.A12 (GND), J_FLASH.B1 (GND), J_FLASH.B12 (GND), J_FLASH.S1 (SHIELD), J_GNSS1.2 (Ext), J_LTE1.4, J_LTE1.9, J_LTE1.15, J_LTE1.18, J_LTE1.21, J_LTE1.26, J_LTE1.27, J_LTE1.29, J_LTE1.34, J_LTE1.35, J_LTE1.37, J_LTE1.40, J_LTE1.43, J_LTE1.50, J_LTEDBG.1, J_PANEL.3, J_PANEL.9, J_PANEL.11, J_PANEL.13, J_PANEL.18, J_PMIC.2, J_PWRBTN.2, J_RB9603.10, J_RB9704.1, J_RB9704.4, J_RB9704.10, J_RB9704.16, J_RPIBOOT.2, J_RTL1.4 (GND), J_RTL1.5 (Shield), J_SIM1.5 (GND), J_SIM1.SH, J_TD2.2, J_WP.2, J_ZBDBG.2, LED1.1 (K), LED3.1 (K), LED4.1 (K), LED6.1 (K), Q1.2 (S), R2.2, R3.2, R4.2, R27.2, R36.2, R38.2, R40.2, R42.2, R50.2, R51.2, R55.2, R61.2, TP2.1, U1.13, U1.19, U1.65, U2.2 (GND), U4.2 (GND), U5.3 (GND), U5.7 (A0), U5.8 (A1), U6.2 (GND), U7.2 (GND), U8.2 (GND), U9.2 (GND), U10.2 (GND), U13.4 (GND), U13.7 (GND), U14.3 (GND), U14.8 (A1), U20.2 (A1), U20.3 (A2), U20.12 (VSS), U20.21 (A0), U21.2 (A1), U21.12 (VSS), U30A.1 (GND), U30A.2 (GND), U30A.7 (GND), U30A.8 (GND), U30A.13 (GND), U30A.14 (GND), U30A.22 (GND), U30A.23 (GND), U30A.32 (GND), U30A.33 (GND), U30A.42 (GND), U30A.43 (GND), U30A.52 (GND), U30A.53 (GND), U30A.59 (GND), U30A.60 (GND), U30A.65 (GND), U30A.66 (GND), U30A.71 (GND), U30A.74 (GND), U30A.98 (GND), U30B.107 (GND), U30B.108 (GND), U30B.113 (GND), U30B.114 (GND), U30B.119 (GND), U30B.120 (GND), U30B.125 (GND), U30B.126 (GND), U30B.131 (GND), U30B.132 (GND), U30B.137 (GND), U30B.138 (GND), U30B.144 (GND), U30B.150 (GND), U30B.155 (GND), U30B.156 (GND), U30B.161 (GND), U30B.162 (GND), U30B.167 (GND), U30B.168 (GND), U30B.173 (GND), U30B.174 (GND), U30B.179 (GND), U30B.180 (GND), U30B.185 (GND), U30B.186 (GND), U30B.191 (GND), U30B.192 (GND), U30B.197 (GND), U30B.198 (GND), U31.1 (GND), U32.1 (GND), U33.3 (GND), U33.7 (A0), U34.1 (VCCA), U40.7 (VDD_USB), U40.10 (GND), U40.12 (GND), U40.13 (GND), U40.24 (GND), U41.7, U41.10, U42.1, U42.11, U42.12, U42.19, U42.23, U42.34, Y1.2 (G), Y1.4 (G)

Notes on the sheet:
POWER INPUT, RAILS, TEST POINTS
3.3 V BUCKS: U31 BOARD (FOLLOWS THE CM5 3.3 V), U32 LTE SOCKET (EN_LTE, 0x44)
COMPUTE MODULE 5 (2x AMPHENOL 10164227-1004A1RLF)
CM5 SUPPORT: RTC CELL, LEDS, FAN, FLASH PORT, BENCH HEADERS
DOMAIN BOUNDARY: 2N7002 STAGES (SHDN_REQ, KILL, TR_APRS), TCA9517A I2C BUFFER
USB 2.0 HUB USB2517I ON THE CM5 USB3-0 PAIR
CH1 SDR BAY: RTL-SDR V4 or LimeSDR Mini 2.0 (0x40)
LTE: MINI PCIe SOCKET (QUECTEL EG25-G) ON THE CM5 USB3-1 PAIR, NANO-SIM
GNSS u-blox NEO-M9N ON I2C (0x42) + PPS, ANTENNA BIAS TEE
LoRa SEEED Wio-SX1262 ON SPI0 CE1
ZIGBEE EBYTE E72-2G4M20S1E (CC2652P, ZNP) ON UART1
TOUCH DISPLAY 2 ON MIPI0 (22-PIN FPC)
I2C EXPANDERS PCA9555 0x20 + 0x25
ROCKBLOCK SITE ON UART2: 9704 + 9603 CONNECTORS, OnOff BUFFER, CH4 5 V (0x43, 2A)
PANEL RIBBON (PCB-C CONTROL PANEL)
DCF77 + A-B INTERCONNECT 2x9 (I2S, GATED 3.3 V FOR THE CODEC)

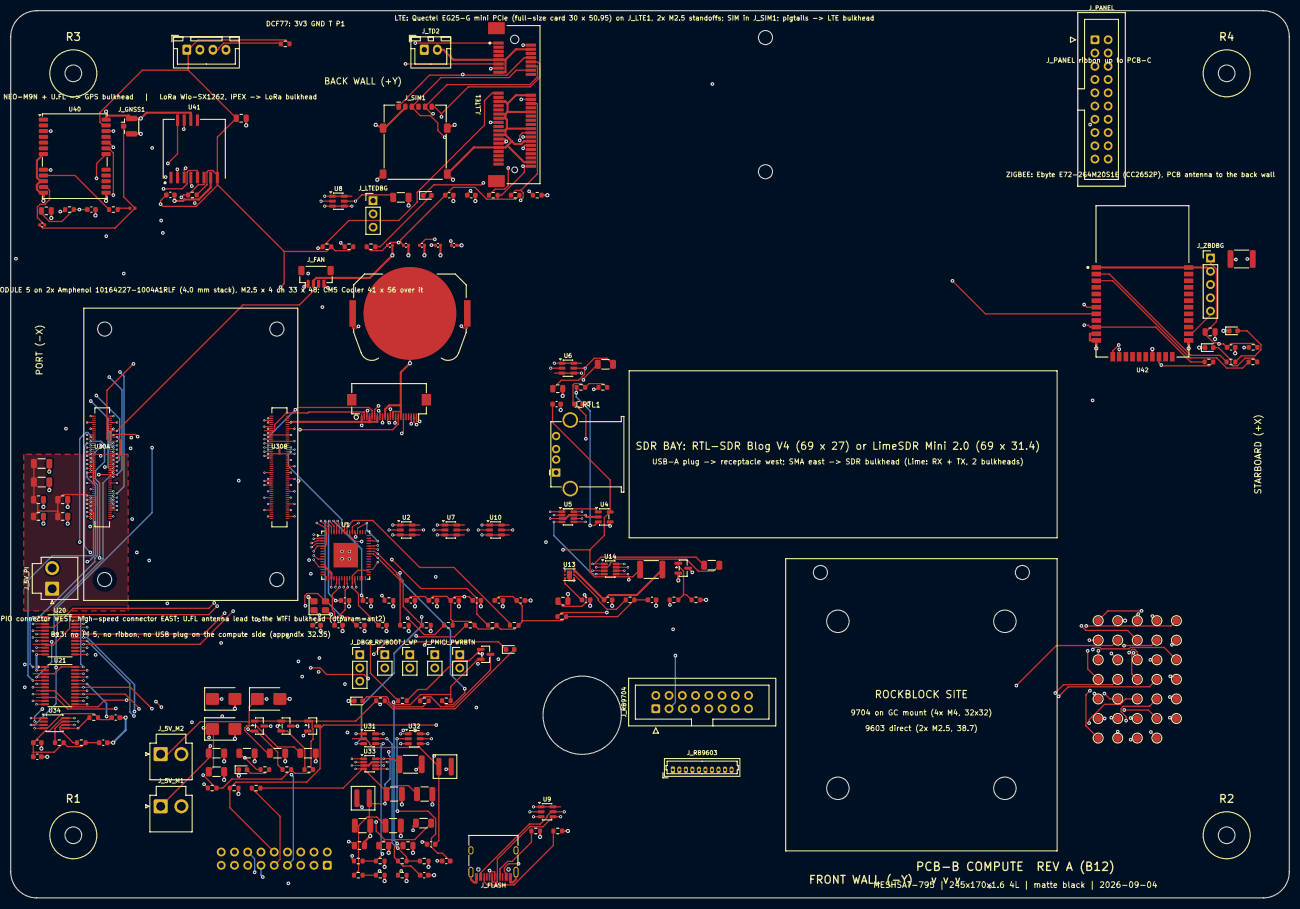
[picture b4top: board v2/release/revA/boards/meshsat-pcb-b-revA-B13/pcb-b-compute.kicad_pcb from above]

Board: 4 copper layers, 245.0 x 170.0 mm, 230 parts (1 on the bottom side), 165 nets.

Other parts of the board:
H1: M3 rod R1; MountingHole_3.2mm_M3
H2: M3 rod R2; MountingHole_3.2mm_M3
H3: M3 rod R3; MountingHole_3.2mm_M3
H4: M3 rod R4; MountingHole_3.2mm_M3
H5, H6, H7, H8: M2.5 standoff 4.0 mm, CM5; MountingHole_2.7mm_M2.5
H9, H10, H11, H12: M4, GC 9704 bracket; MountingHole_4.3mm_M4
H13, H14: M2.5, RockBLOCK 9603; MountingHole_2.7mm_M2.5
S_RTL1, S_RTL2, S_RTL3, S_RTL4: tie slot; Slot_5x1.8_NPTH
